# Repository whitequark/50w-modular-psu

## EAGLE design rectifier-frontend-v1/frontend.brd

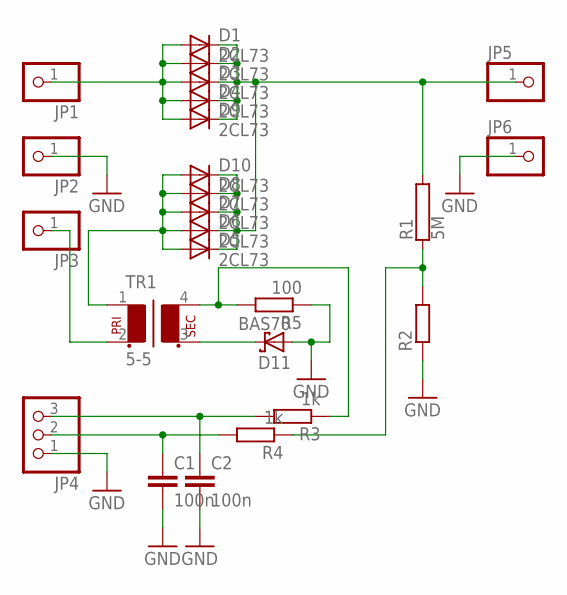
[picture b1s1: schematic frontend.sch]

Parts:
C1, C2: 100n; C1206
D1, D2, D3, D4, D5, D6, D7, D8, D9, D10: 2CL73; DIODE-3-20
D11: BAS70; SOT23
JP1, JP2, JP3, JP5, JP6: PINHD-1X1; 1X01
JP4: PINHD-1X3/90; 1X03/90
R1: 5M; CA4150
R2: R-EU_R0805; R0805
R3, R4: 1k; R0805
R5: 100; R0805
TR1: 5-5; RM4-4

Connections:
GND: C1.2, C2.2, D11.1 (A), JP2.1, JP4.1, JP6.1, R2.1, R5.1
unnamed: D1.A, D2.A, D3.A, D4.A, D9.A, JP1.1
unnamed: R1.1, R2.2, R4.1
unnamed: D5.A, D6.A, D7.A, D8.A, D10.A, TR1.1
unnamed: D1.C, D2.C, D3.C, D4.C, D5.C, D6.C, D7.C, D8.C, D9.C, D10.C, JP5.1, R1.2
unnamed: C1.1, JP4.2, R4.2
unnamed: C2.1, JP4.3, R3.2
unnamed: JP3.1, TR1.2
unnamed: R3.1, R5.2, TR1.4
unnamed: D11.3 (C), TR1.3

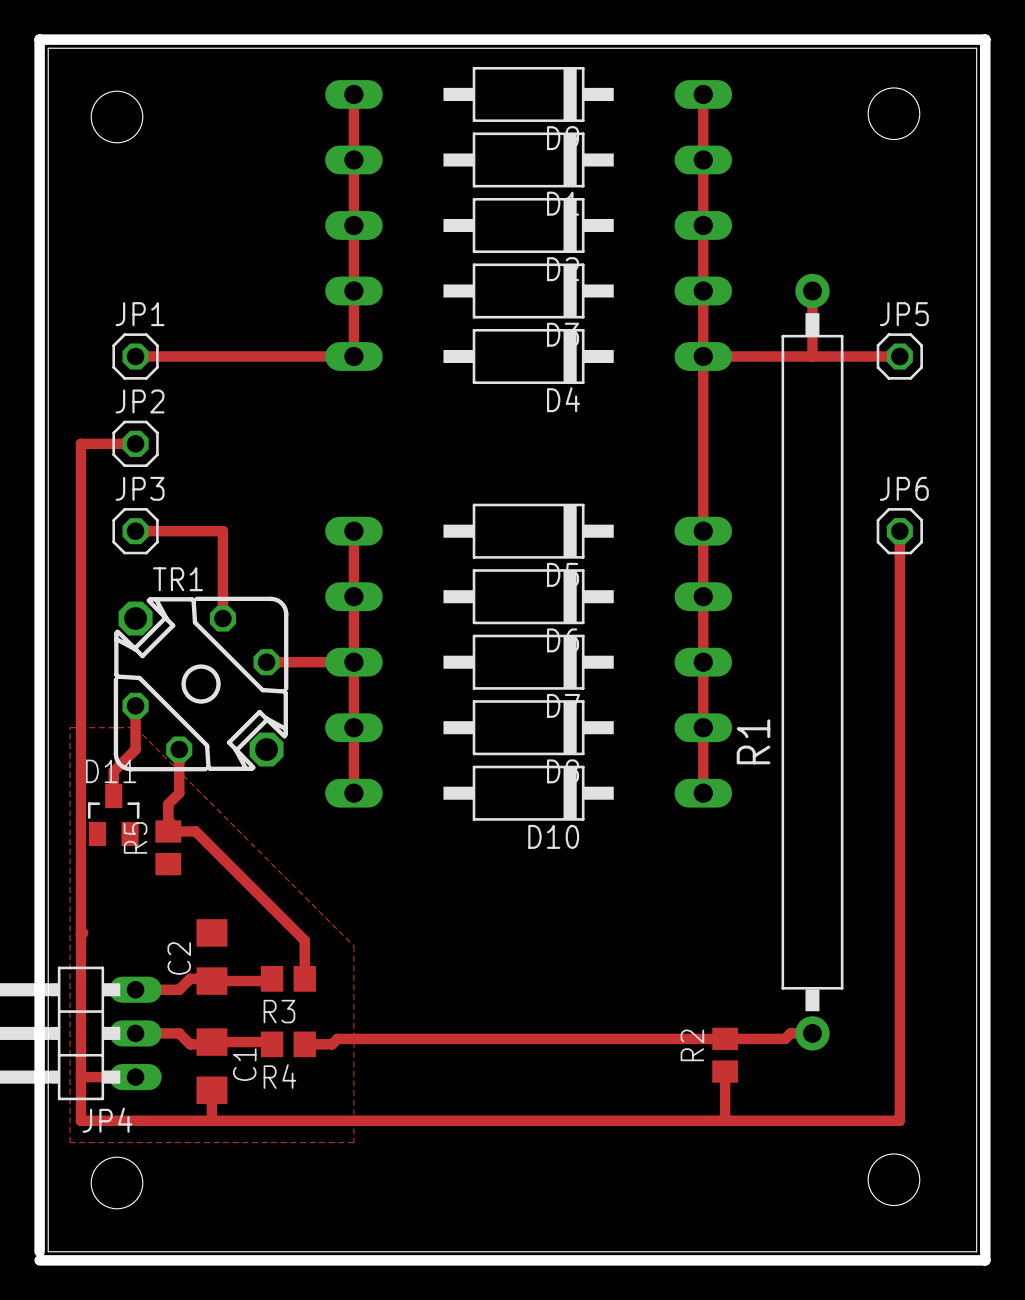
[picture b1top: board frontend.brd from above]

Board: 2 copper layers, 55.0 x 71.0 mm, 25 parts (0 on the bottom side), 10 nets.

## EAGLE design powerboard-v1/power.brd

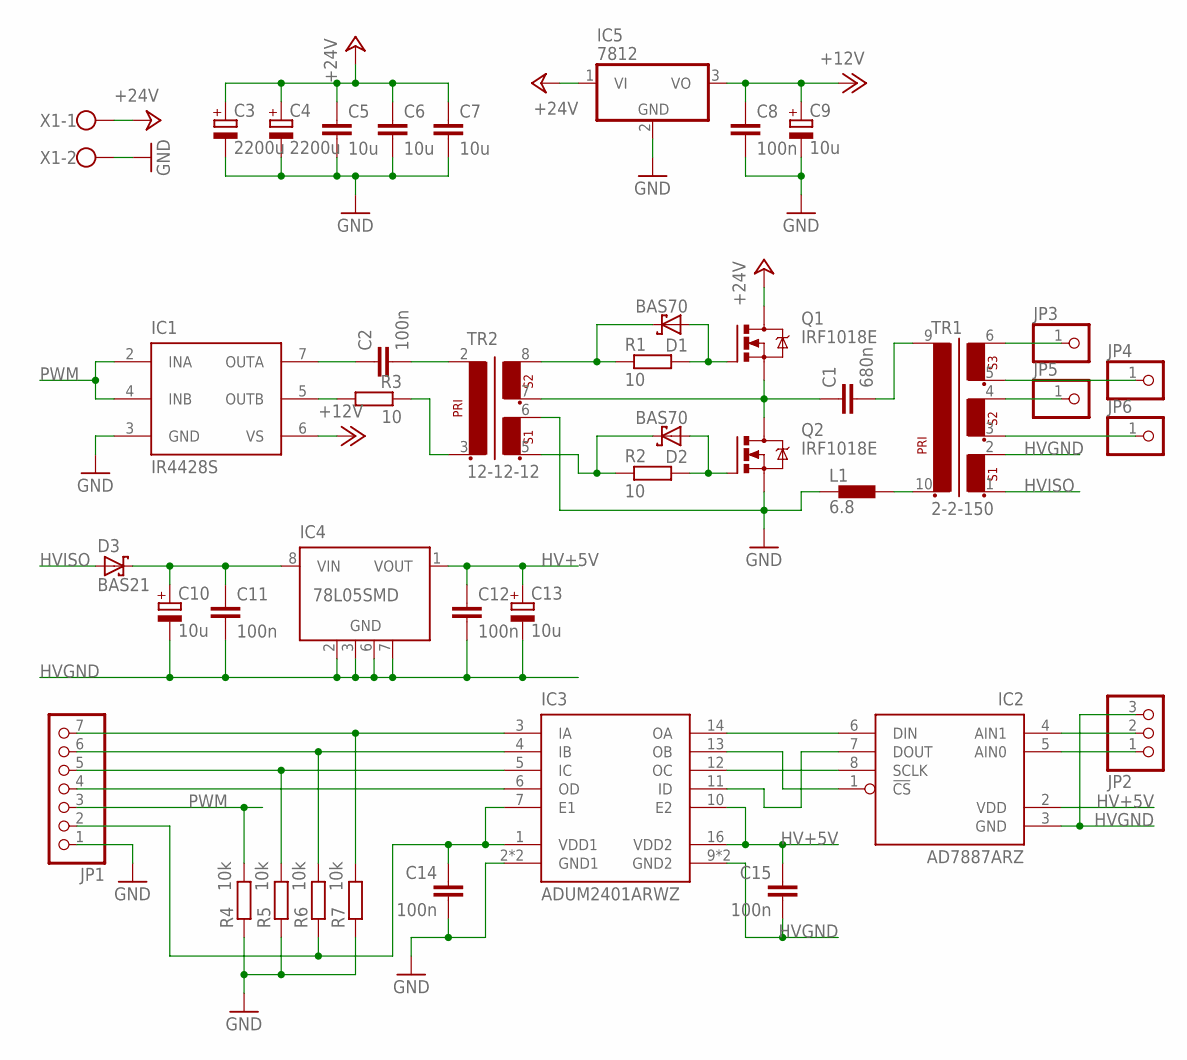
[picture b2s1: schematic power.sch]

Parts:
C1: 680n; C150-084X183
C2, C8, C11, C12, C14, C15: 100n; C1206
C3, C4: 2200u; E7,5-16
C5, C6, C7: 10u; C1210
C9, C10, C13: 10u; B/3528-21R
D1, D2: BAS70; SOT23
D3: BAS21; SOT23
IC1: IR4428S; SO08
IC2: AD7887ARZ; SO08
IC3: ADUM2401ARWZ; SO-16W
IC4: 78L05SMD; SO08
IC5: 7812; D2PACK
JP1: PINHD-1X7/90; 1X07/90
JP2: PINHD-1X3/90; 1X03/90
JP3, JP4, JP5, JP6: PINHD-1X1; 1X01
L1: 6.8; TSL1112
Q1, Q2: IRF1018E; TO220BV
R1, R2, R3: 10; R0805
R4, R5, R6, R7: 10k; R0805
TR1: 2-2-150; RM12T1
TR2: 12-12-12; RM5LS
X1: W237-102

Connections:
!CS: IC3.3 (IA), JP1.7, R7.2
+12V: C8.1, C9.+, IC1.6 (VS), IC5.3 (VO)
+24V: C3.+, C4.+, C5.1, C6.1, C7.1, IC5.1 (VI), Q1.D, X1.1
AIN1: IC2.4 (AIN1), JP2.2
DIN: IC3.5 (IC), JP1.5, R5.2
DOUT: IC3.6 (OD), JP1.4
GND: C3.-, C4.-, C5.2, C6.2, C7.2, C8.2, C9.-, C14.2, IC1.3 (GND), IC3.2 (GND1), IC3.8 (GND1), IC5.2 (GND), JP1.1, L1.P$1 (1), Q2.S, R4.1, R5.1, R7.1, TR2.6 (4), X1.2
HV+5V: C12.1, C13.+, C15.1, IC2.2 (VDD), IC3.10 (E2), IC3.16 (VDD2), IC4.1 (VOUT)
HVGND: C10.-, C11.2, C12.2, C13.-, C15.2, IC2.3 (GND), IC3.9 (GND2), IC3.15 (GND2), IC4.2 (GND), IC4.3 (GND), IC4.6 (GND), IC4.7 (GND), JP2.3, TR1.2 (4)
HVISO: D3.1 (A), TR1.1 (3)
unnamed: C1.1, Q1.S, Q2.D, TR2.7 (5)
unnamed: D1.3 (C), R1.1, TR2.8 (6)
unnamed: D2.1 (A), Q2.G, R2.2
unnamed: C1.2, TR1.9 (1)
unnamed: D1.1 (A), Q1.G, R1.2
unnamed: D2.3 (C), R2.1, TR2.5 (3)
unnamed: C10.+, C11.1, D3.3 (C), IC4.8 (VIN)
unnamed: C2.1, IC1.7 (OUTA)
unnamed: R3.1, TR2.3 (2)
unnamed: C2.2, TR2.2 (1)
unnamed: C14.1, IC3.1 (VDD1), IC3.7 (E1), JP1.2, R6.1
unnamed: IC2.1 (!CS), IC3.13 (OB)
unnamed: IC2.8 (SCLK), IC3.12 (OC)
unnamed: IC2.7 (DOUT), IC3.11 (ID)
unnamed: IC2.5 (AIN0), JP2.1
unnamed: IC2.6 (DIN), IC3.14 (OA)
unnamed: L1.P$2 (2), TR1.10 (2)
unnamed: JP3.1, TR1.6 (8)
unnamed: JP4.1, TR1.5 (7)
unnamed: JP5.1, TR1.4 (6)
unnamed: JP6.1, TR1.3 (5)
unnamed: IC1.5 (OUTB), R3.2
PWM: IC1.2 (INA), IC1.4 (INB), JP1.3, R4.2
SCLK: IC3.4 (IB), JP1.6, R6.2

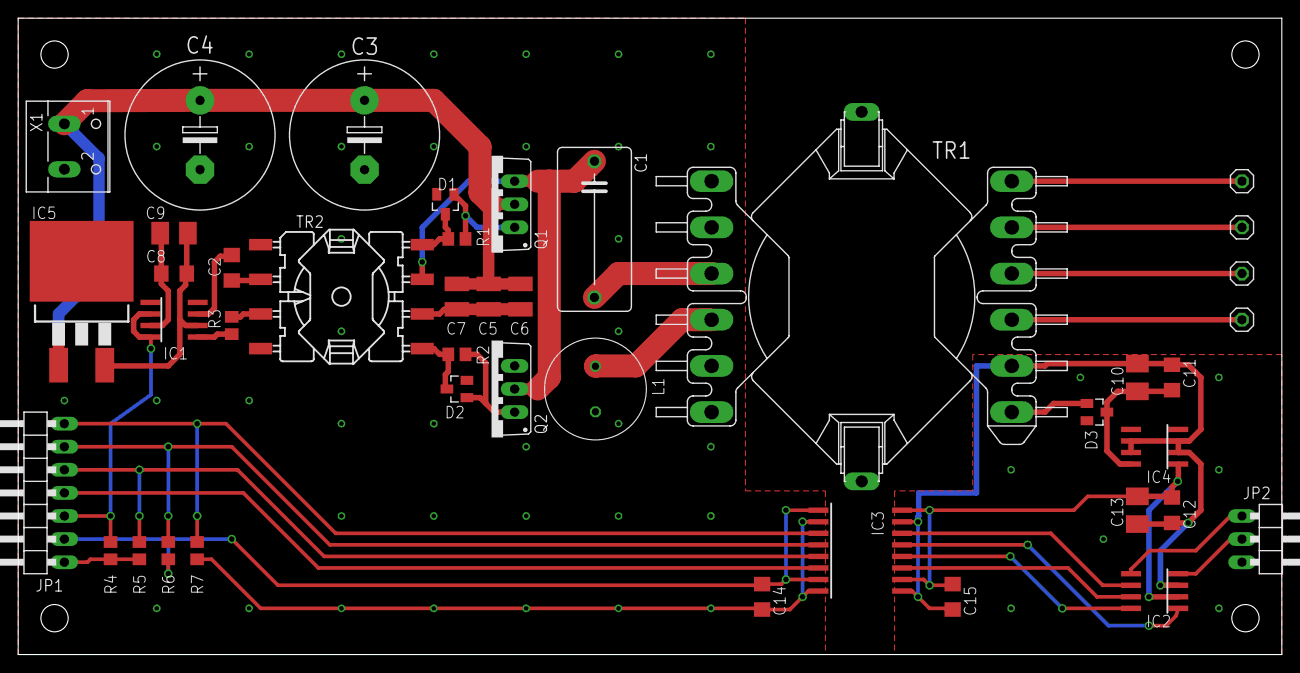
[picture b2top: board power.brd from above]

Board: 2 copper layers, 139.0 x 70.0 mm, 42 parts (0 on the bottom side), 34 nets.

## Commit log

2015-01-08 Initial commit.
2015-01-08 Add license.
2015-01-08 Fix clearance issues.
2015-02-03 Add FIXME
2015-02-04 Add Maple firmware.
2015-02-04 Add BAT70 datasheet.
2015-02-04 Add more fail to FIXME.
2015-02-04 Even more fail in FIXME.
2015-02-05 Fix a mislabeled pin.
2015-02-05 Add ADC reading to firmware.
2015-02-06 Phase-lock ADC to PWM out.
2015-02-06 Remove FIXME as the lab note is written.
2015-02-06 D3: BAS70->BAS21.
2015-02-06 Restructure firmware folder.
2015-02-06 Update schematics wrt BAS21.
2015-02-14 Add preliminary rectifier frontend.
